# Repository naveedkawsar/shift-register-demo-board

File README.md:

# shift-register-demo-board
Test breakout PCB containing JLCPCB basic peripherals for testing with MCU dev kits
<!--

-->

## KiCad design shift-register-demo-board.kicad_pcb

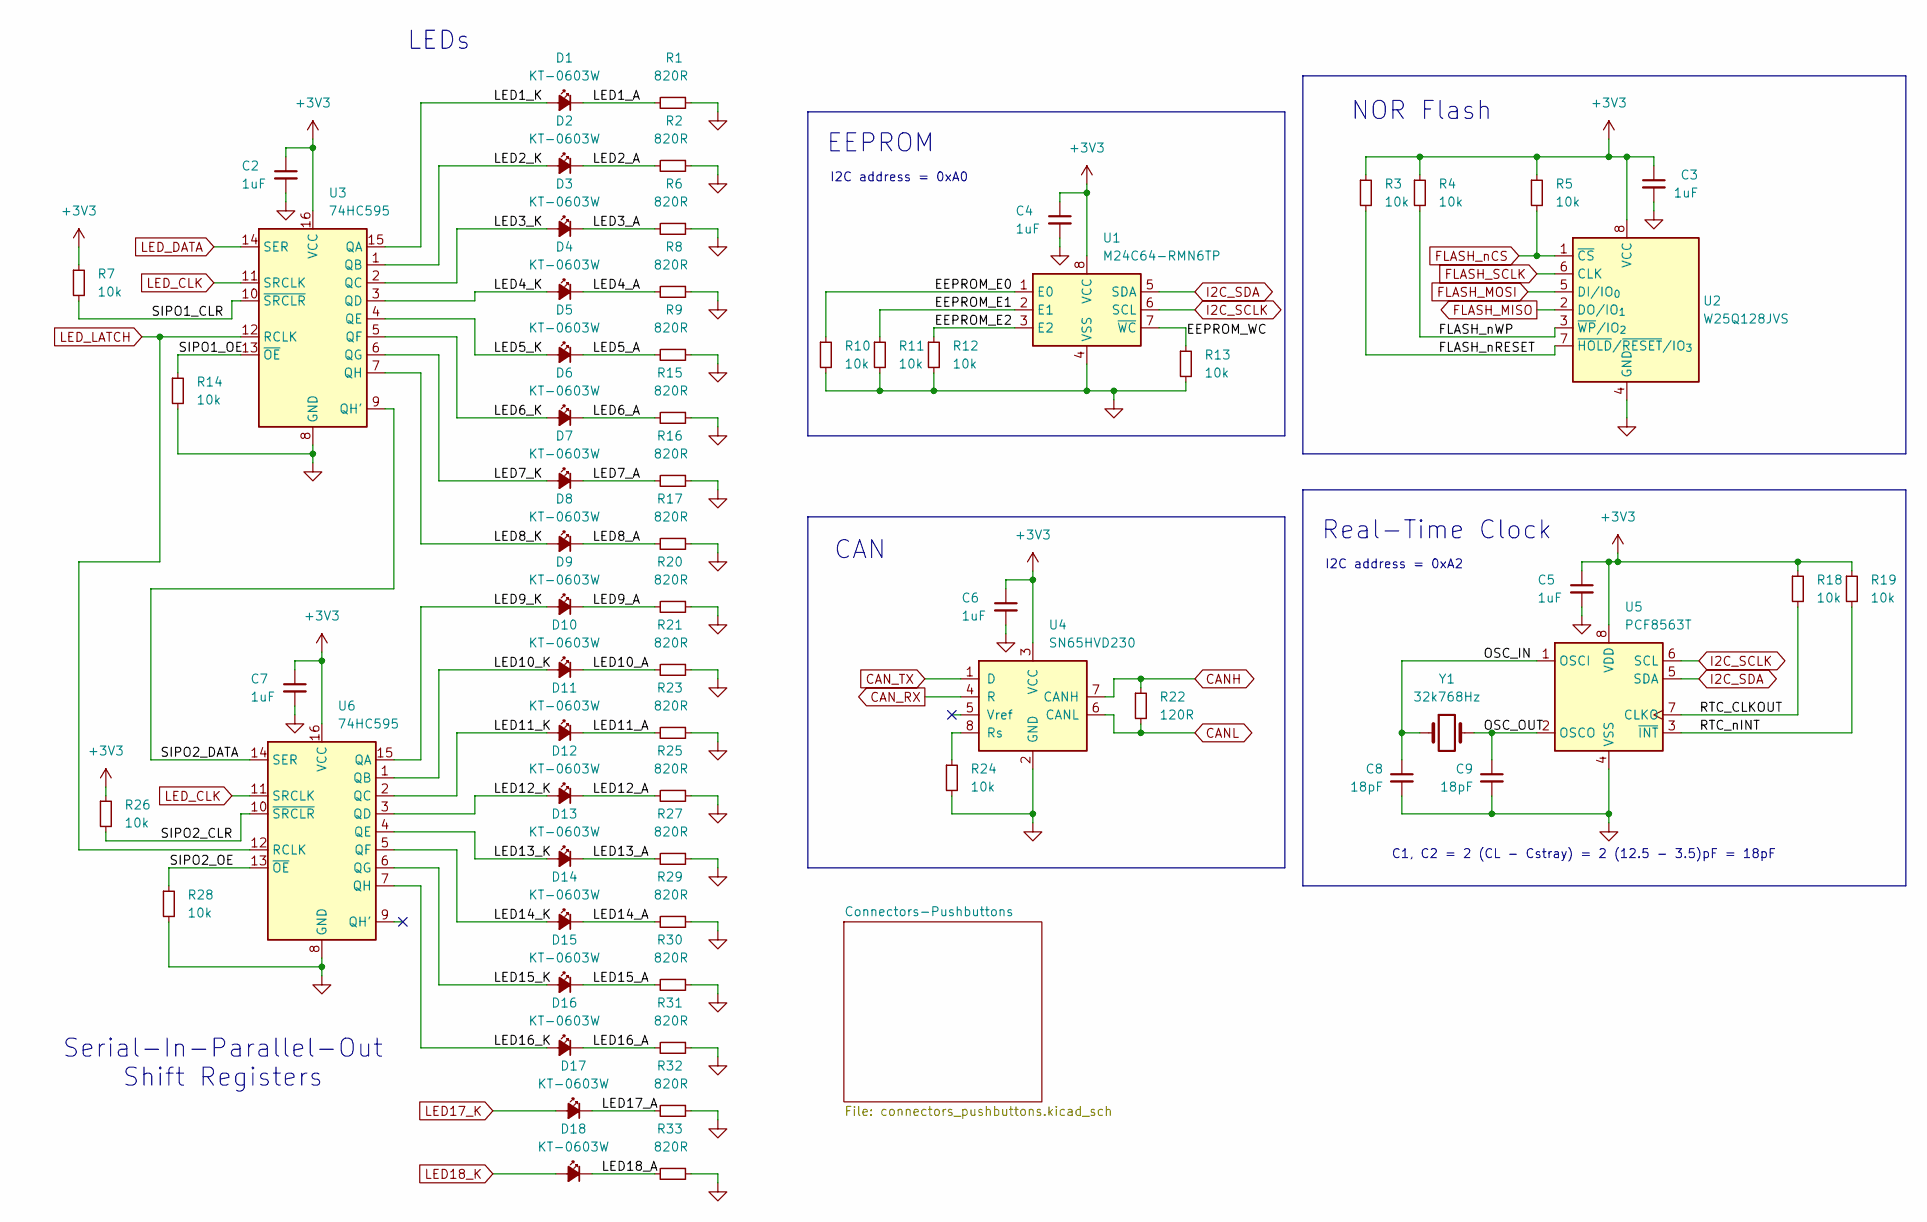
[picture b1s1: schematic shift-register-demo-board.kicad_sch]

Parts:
C2, C3, C4, C5, C6, C7: 1uF; C_0603_1608Metric; Voltage 50V; Manufacturer Part Number CL10A105KB8NNNC; LCSC Part # C15849
C8, C9: 18pF; C_0603_1608Metric; Voltage 50V; Manufacturer Part Number CL10C180JB8NNNC; LCSC Part # C1647
D1, D2, D3, D4, D5, D6, D7, D8, D9, D10, D11, D12, D13, D14, D15, D16, D17, D18: KT-0603W; LED_0603_1608Metric; Manufacturer Part Number KT-0603W; LCSC Part # C2290
R1, R2, R6, R8, R9, R15, R16, R17, R20, R21, R23, R25, R27, R29, R30, R31, R32, R33: 820R; R_0603_1608Metric; Manufacturer Part Number 0603WAF8200T5E; LCSC Part # C23253
R3, R4, R5, R7, R10, R11, R12, R13, R14, R18, R19, R24, R26, R28: 10k; R_0603_1608Metric; Voltage 75V; Manufacturer Part Number 0603WAF1002T5E; LCSC Part # C25804
R22: 120R; R_0603_1608Metric; Voltage 75V; Manufacturer Part Number 0603WAF1200T5E; LCSC Part # C22787
U1: M24C64-RMN6TP; SOIC-8_3.9x4.9mm_P1.27mm; LCSC Part # C79988
U2: W25Q128JVS; SOIC-8_5.3x5.3mm_P1.27mm; Manufacturer Part Number W25Q128JVSIQ; LCSC Part # C97521
U3, U6: 74HC595; SOIC-16_3.9x9.9mm_P1.27mm; LCSC Part # C5947
U4: SN65HVD230; SOIC-8_3.9x4.9mm_P1.27mm; Manufacturer Part Number SN65HVD230DR; LCSC Part # C12084
U5: PCF8563T; SOIC-8_3.9x4.9mm_P1.27mm; Manufacturer Part Number PCF8563T/5,518; LCSC Part # C7440
Y1: 32k768Hz; Crystal_SMD_3215-2Pin_3.2x1.5mm; Manufacturer Part Number Q13FC13500004; LCSC Part # C32346

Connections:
+3V3: C2.1, C3.1, C4.1, C5.1, C6.1, C7.1, R3.1, R4.1, R5.1, R7.1, R18.1, R19.1, R26.1, U1.8 (VCC), U2.8 (VCC), U3.16 (VCC), U4.3 (VCC), U5.8 (VDD), U6.16 (VCC); also elsewhere on the board
/EEPROM_E0: R10.1, U1.1 (E0)
/EEPROM_E1: R11.1, U1.2 (E1)
/EEPROM_E2: R12.1, U1.3 (E2)
/EEPROM_WC: R13.1, U1.7 (~WC)
/FLASH_nRESET: R3.2, U2.7 (~HOLD/~RESET/IO_{3})
/FLASH_nWP: R4.2, U2.3 (~WP/IO_{2})
/LED1_A: D1.1 (K), R1.2
/LED1_K: D1.2 (A), U3.15 (QA)
/LED2_A: D2.1 (K), R2.2
/LED2_K: D2.2 (A), U3.1 (QB)
/LED3_A: D3.1 (K), R6.2
/LED3_K: D3.2 (A), U3.2 (QC)
/LED4_A: D4.1 (K), R8.2
/LED4_K: D4.2 (A), U3.3 (QD)
/LED5_A: D5.1 (K), R9.2
/LED5_K: D5.2 (A), U3.4 (QE)
/LED6_A: D6.1 (K), R15.2
/LED6_K: D6.2 (A), U3.5 (QF)
/LED7_A: D7.1 (K), R16.2
/LED7_K: D7.2 (A), U3.6 (QG)
/LED8_A: D8.1 (K), R17.2
/LED8_K: D8.2 (A), U3.7 (QH)
/LED9_A: D9.1 (K), R20.2
/LED9_K: D9.2 (A), U6.15 (QA)
/LED10_A: D10.1 (K), R21.2
/LED10_K: D10.2 (A), U6.1 (QB)
/LED11_A: D11.1 (K), R23.2
/LED11_K: D11.2 (A), U6.2 (QC)
/LED12_A: D12.1 (K), R25.2
/LED12_K: D12.2 (A), U6.3 (QD)
/LED13_A: D13.1 (K), R27.2
/LED13_K: D13.2 (A), U6.4 (QE)
/LED14_A: D14.1 (K), R29.2
/LED14_K: D14.2 (A), U6.5 (QF)
/LED15_A: D15.1 (K), R30.2
/LED15_K: D15.2 (A), U6.6 (QG)
/LED16_A: D16.1 (K), R31.2
/LED16_K: D16.2 (A), U6.7 (QH)
/LED17_A: D17.1 (K), R32.2
/LED18_A: D18.1 (K), R33.2
/OSC_IN: C8.1, U5.1 (OSCI), Y1.1
/OSC_OUT: C9.1, U5.2 (OSCO), Y1.2
/RTC_CLKOUT: R18.2, U5.7 (CLKO)
/RTC_nINT: R19.2, U5.3 (~INT)
/SIPO1_CLR: R7.2, U3.10 (~SRCLR)
/SIPO1_OE: R14.1, U3.13 (~OE)
/SIPO2_CLR: R26.2, U6.10 (~SRCLR)
/SIPO2_DATA: U3.9 (QH'), U6.14 (SER)
/SIPO2_OE: R28.1, U6.13 (~OE)
CANH: R22.1, U4.7 (CANH); also elsewhere on the board
CANL: R22.2, U4.6 (CANL); also elsewhere on the board
CAN_RX: U4.4 (R); also elsewhere on the board
CAN_TX: U4.1 (D); also elsewhere on the board
FLASH_MISO: U2.2 (DO/IO_{1}); also elsewhere on the board
FLASH_MOSI: U2.5 (DI/IO_{0}); also elsewhere on the board
FLASH_SCLK: U2.6 (CLK); also elsewhere on the board
FLASH_nCS: R5.2, U2.1 (~CS); also elsewhere on the board
GND: C2.2, C3.2, C4.2, C5.2, C6.2, C7.2, C8.2, C9.2, R1.1, R2.1, R6.1, R8.1, R9.1, R10.2, R11.2, R12.2, R13.2, R14.2, R15.1, R16.1, R17.1, R20.1, R21.1, R23.1, R24.2, R25.1, R27.1, R28.2, R29.1, R30.1, R31.1, R32.1, R33.1, U1.4 (VSS), U2.4 (GND), U3.8 (GND), U4.2 (GND), U5.4 (VSS), U6.8 (GND); also elsewhere on the board
I2C_SCLK: U1.6 (SCL), U5.6 (SCL); also elsewhere on the board
I2C_SDA: U1.5 (SDA), U5.5 (SDA); also elsewhere on the board
LED17_K: D17.2 (A); also elsewhere on the board
LED18_K: D18.2 (A); also elsewhere on the board
LED_CLK: U3.11 (SRCLK), U6.11 (SRCLK); also elsewhere on the board
LED_DATA: U3.14 (SER); also elsewhere on the board
LED_LATCH: U3.12 (RCLK), U6.12 (RCLK); also elsewhere on the board
unnamed: R24.1, U4.8 (Rs)

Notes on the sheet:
EEPROM
LEDs
NOR Flash
CAN
I2C address = 0xA0
C1, C2 = 2 (CL - Cstray) = 2 (12.5 - 3.5)pF = 18pF
I2C address = 0xA2
Serial-In-Parallel-Out Shift Registers
Real-Time Clock

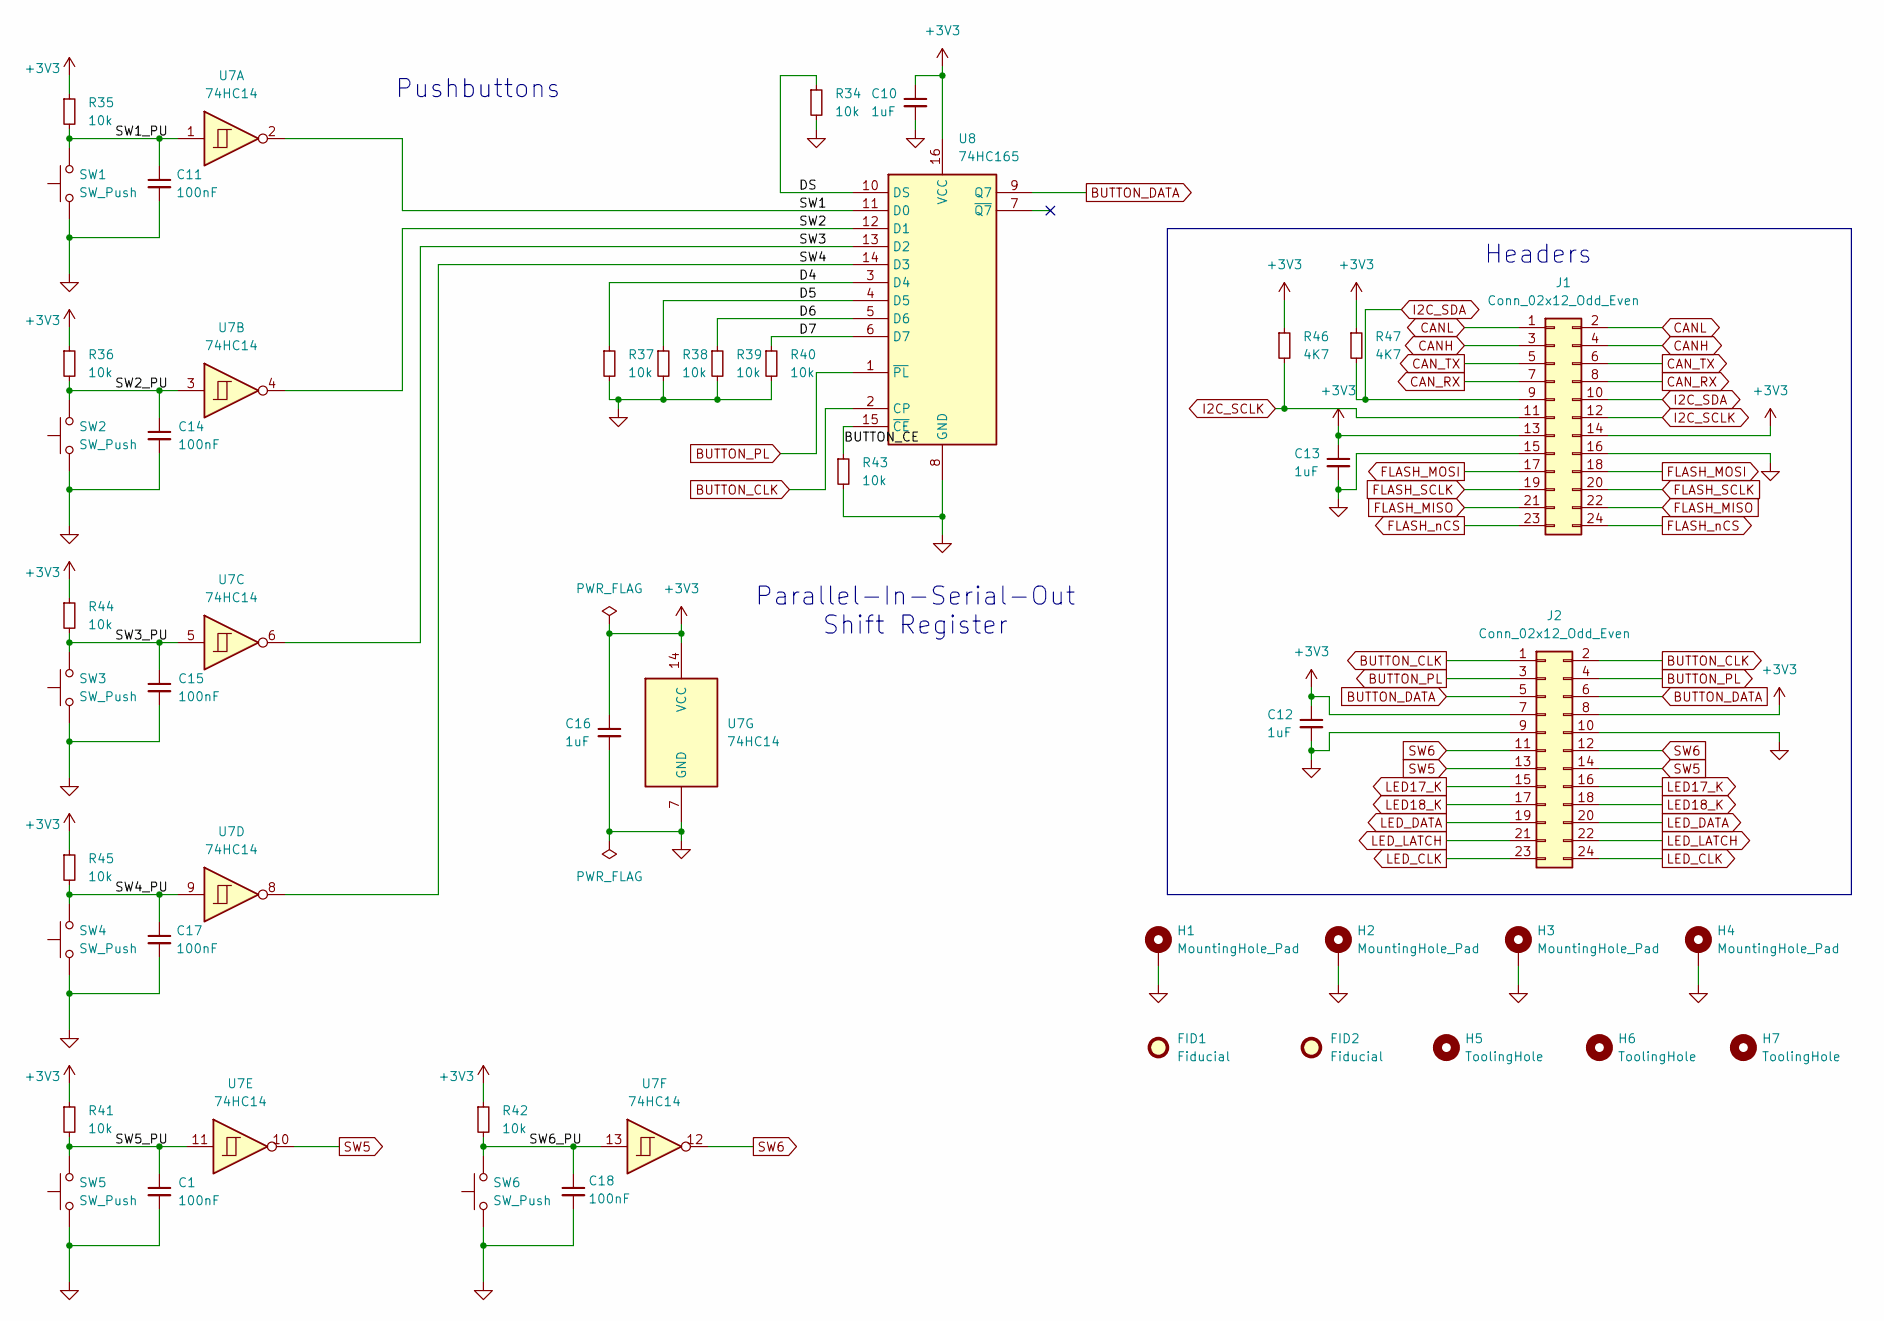
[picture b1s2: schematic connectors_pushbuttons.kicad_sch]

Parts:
C1, C11, C14, C15, C17, C18: 100nF; C_0603_1608Metric; Voltage 50V; Manufacturer Part Number CC0603KRX7R9BB104; LCSC Part # C14663
C10, C12, C13, C16: 1uF; C_0603_1608Metric; Voltage 50V; Manufacturer Part Number CL10A105KB8NNNC; LCSC Part # C15849
FID1, FID2: Fiducial; Fiducial_1mm_Mask2mm
H1, H2, H3, H4: MountingHole_Pad; MountingHole_3.2mm_M3_Pad
H5, H6, H7: ToolingHole; JLCPCB_ToolingHole_45.4mils
J1, J2: Conn_02x12_Odd_Even; PinHeader_2x12_P2.54mm_Vertical
R34, R35, R36, R37, R38, R39, R40, R41, R42, R43, R44, R45: 10k; R_0603_1608Metric; Voltage 75V; Manufacturer Part Number 0603WAF1002T5E; LCSC Part # C25804
R46, R47: 4K7; R_0603_1608Metric; Voltage 75V; Manufacturer Part Number 0603WAF4701T5E; LCSC Part # C23162
SW1, SW2, SW3, SW4, SW5, SW6: SW_Push; SW_Push_1P1T_XKB_TS-1187A; LCSC Part # C318884
U7: 74HC14; SO-14_3.9x8.65mm_P1.27mm
U8: 74HC165; SOIC-16_3.9x9.9mm_P1.27mm; LCSC Part # C5613

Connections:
+3V3: C10.1, C12.1, C13.1, C16.1, J1.13, J1.14, J2.7, J2.8, R35.1, R36.1, R41.1, R42.1, R44.1, R45.1, R46.1, R47.1, U7.14 (VCC), U8.16 (VCC); also elsewhere on the board
/Connectors-Pushbuttons/BUTTON_CE: R43.1, U8.15 (~CE)
/Connectors-Pushbuttons/D4: R37.1, U8.3 (D4)
/Connectors-Pushbuttons/D5: R38.1, U8.4 (D5)
/Connectors-Pushbuttons/D6: R39.1, U8.5 (D6)
/Connectors-Pushbuttons/D7: R40.1, U8.6 (D7)
/Connectors-Pushbuttons/DS: R34.1, U8.10 (DS)
/Connectors-Pushbuttons/SW1: U7.2, U8.11 (D0)
/Connectors-Pushbuttons/SW1_PU: C11.1, R35.2, SW1.2, U7.1
/Connectors-Pushbuttons/SW2: U7.4, U8.12 (D1)
/Connectors-Pushbuttons/SW2_PU: C14.1, R36.2, SW2.2, U7.3
/Connectors-Pushbuttons/SW3: U7.6, U8.13 (D2)
/Connectors-Pushbuttons/SW3_PU: C15.1, R44.2, SW3.2, U7.5
/Connectors-Pushbuttons/SW4: U7.8, U8.14 (D3)
/Connectors-Pushbuttons/SW4_PU: C17.1, R45.2, SW4.2, U7.9
/Connectors-Pushbuttons/SW5_PU: C1.1, R41.2, SW5.2, U7.11
/Connectors-Pushbuttons/SW6_PU: C18.1, R42.2, SW6.2, U7.13
BUTTON_CLK: J2.1, J2.2, U8.2 (CP)
BUTTON_DATA: J2.5, J2.6, U8.9 (Q7)
BUTTON_PL: J2.3, J2.4, U8.1 (~PL)
CANH: J1.3, J1.4; also elsewhere on the board
CANL: J1.1, J1.2; also elsewhere on the board
CAN_RX: J1.7, J1.8; also elsewhere on the board
CAN_TX: J1.5, J1.6; also elsewhere on the board
FLASH_MISO: J1.21, J1.22; also elsewhere on the board
FLASH_MOSI: J1.17, J1.18; also elsewhere on the board
FLASH_SCLK: J1.19, J1.20; also elsewhere on the board
FLASH_nCS: J1.23, J1.24; also elsewhere on the board
GND: C1.2, C10.2, C11.2, C12.2, C13.2, C14.2, C15.2, C16.2, C17.2, C18.2, H1.1, H2.1, H3.1, H4.1, J1.15, J1.16, J2.9, J2.10, R34.2, R37.2, R38.2, R39.2, R40.2, R43.2, SW1.1, SW2.1, SW3.1, SW4.1, SW5.1, SW6.1, U7.7 (GND), U8.8 (GND); also elsewhere on the board
I2C_SCLK: J1.11, J1.12, R46.2; also elsewhere on the board
I2C_SDA: J1.9, J1.10, R47.2; also elsewhere on the board
LED17_K: J2.15, J2.16; also elsewhere on the board
LED18_K: J2.17, J2.18; also elsewhere on the board
LED_CLK: J2.23, J2.24; also elsewhere on the board
LED_DATA: J2.19, J2.20; also elsewhere on the board
LED_LATCH: J2.21, J2.22; also elsewhere on the board
SW5: J2.13, J2.14, U7.10
SW6: J2.11, J2.12, U7.12

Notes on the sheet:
Headers
Parallel-In-Serial-Out Shift Register
Pushbuttons

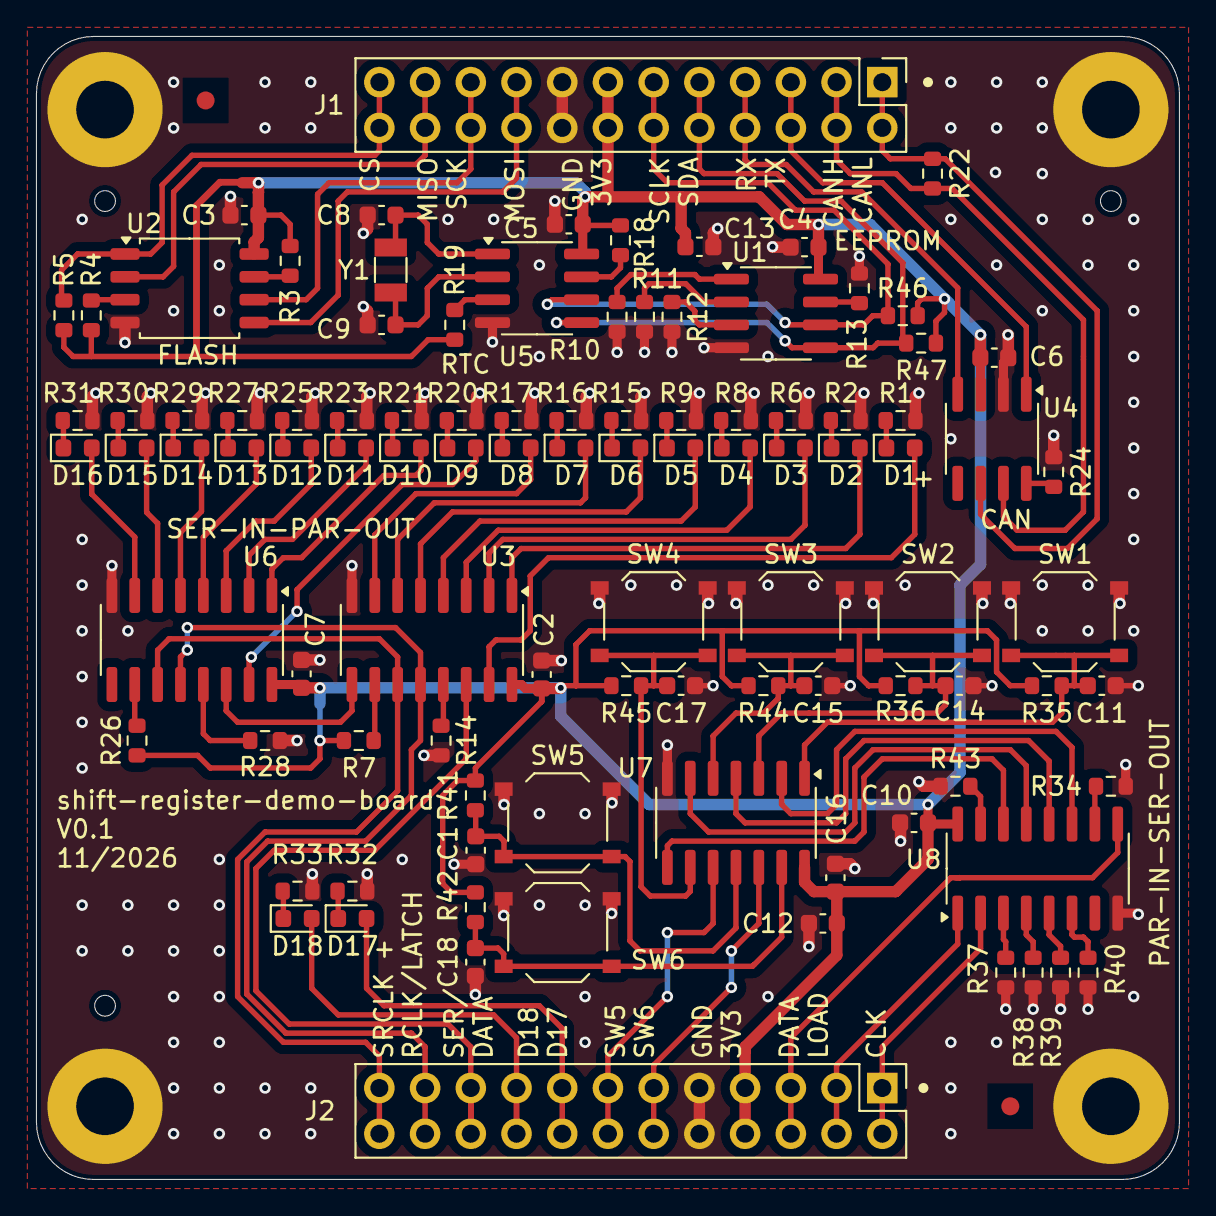
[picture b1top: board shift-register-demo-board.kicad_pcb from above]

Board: 2 copper layers, 63.5 x 63.5 mm, 109 parts (0 on the bottom side), 88 nets.
